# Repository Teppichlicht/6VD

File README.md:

# 6VD
6VDproduct_development

First Changes in Github:
Codesharing for multiuserprogramming in 6VD

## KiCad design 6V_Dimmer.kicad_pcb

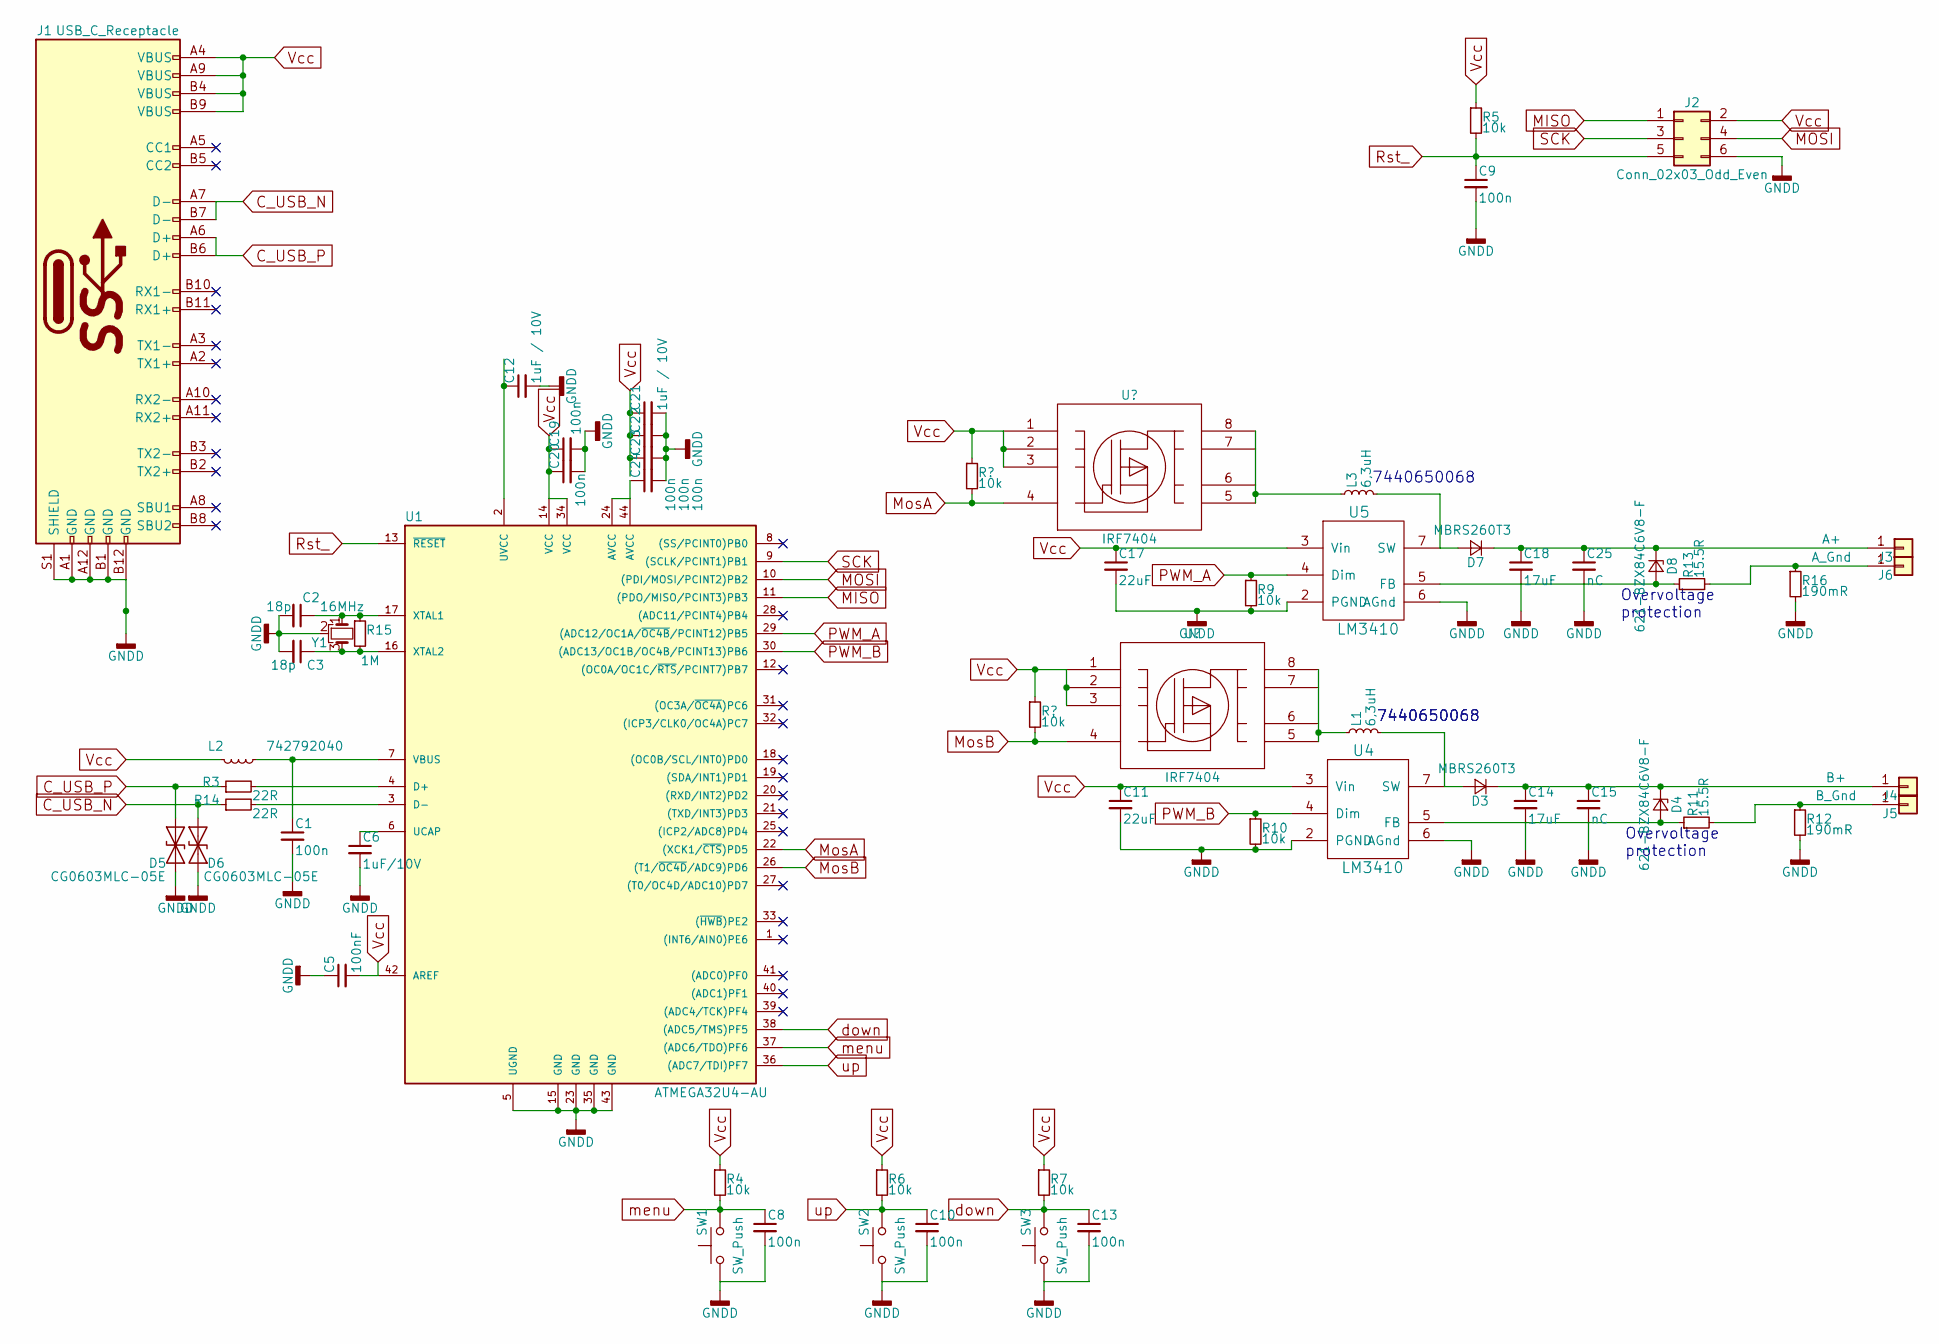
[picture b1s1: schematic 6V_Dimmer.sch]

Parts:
C1, C8, C9, C10, C13, C19, C20, C22, C23, C24: 100n; C_0805_HandSoldering
C2, C3: 18p; C_0805_HandSoldering
C5: 100nF; C_0805_HandSoldering
C6: 1uF/10V; C_0805_HandSoldering
C11, C17: 22uF; C_0805_HandSoldering
C12, C21: 1uF / 10V; C_0805_HandSoldering
C14, C18: 17uF; C_0805_HandSoldering
C15, C25: nC; C_0805_HandSoldering
D3, D7: MBRS260T3; D_SMB
D4, D8: 621-BZX84C6V8-F; D_SOT-23_ANK
D5, D6: CG0603MLC-05E; D_0603
J1: USB_C_Receptacle; USB_C_Receptacle_Amphenol_12401548E4-2A_CircularHoles
J2: Conn_02x03_Odd_Even; Pin_Header_Straight_2x03_Pitch2.54mm
J3: A+; SolderWirePad_single_1-5mmDrill
J4: B+; SolderWirePad_single_1-5mmDrill
J5: B_Gnd; SolderWirePad_single_1-5mmDrill
J6: A_Gnd; SolderWirePad_single_1-5mmDrill
L1, L3: 6,3uH; L_10.4x10.4_H4.8
L2: 742792040; L_0805_HandSoldering
R3, R14: 22R; R_0805_HandSoldering
R4, R5, R6, R7, R9, R10: 10k; R_0805_HandSoldering
R11, R13: 15.5R; R_0805_HandSoldering
R12, R16: 190mR; R_0805_HandSoldering
R15: 1M; R_0805_HandSoldering
SW1, SW2, SW3: SW_Push; SW_SPST_Panasonic_EVQPL_3PL_5PL_PT_A08
U1: ATMEGA32U4-AU; TQFP-44_10x10mm_Pitch0.8mm
U4, U5: LM3410; MSOP-8-1EP_3x3mm_Pitch0.65mm
Y1: 16MHz; Crystal_SMD_Abracon_ABM3B-4pin_5.0x3.2mm

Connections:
C_USB_N: D6.1 (A1), J1.A7 (D-), J1.B7 (D-), R14.1
C_USB_P: D5.1 (A1), J1.A6 (D+), J1.B6 (D+), R3.1
GNDD: C1.2, C2.2, C3.2, C5.1, C6.2, C8.2, C9.2, C10.2, C11.2, C12.2, C13.2, C14.2, C15.2, C17.2, C18.2, C19.2, C20.2, C21.2, C22.2, C23.2, C24.2, C25.2, D5.2 (A2), D6.2 (A2), J1.A1 (GND), J1.A12 (GND), J1.B1 (GND), J1.B12 (GND), J1.S1 (SHIELD), J2.6, R9.2, R10.2, R12.2, R16.2, SW1.1, SW2.1, SW3.1, U1.5 (UGND), U1.15 (GND), U1.23 (GND), U1.35 (GND), U1.43 (GND), U4.2 (PGND), U4.6 (AGnd), U5.2 (PGND), U5.6 (AGnd), Y1.2
MISO: J2.1, U1.11 ((PDO/MISO/PCINT3)PB3)
MOSI: J2.4, U1.10 ((PDI/MOSI/PCINT2)PB2)
unnamed: C1.1, L2.1, U1.7 (VBUS)
unnamed: C2.1, R15.1, U1.17 (XTAL1), Y1.1
unnamed: C3.1, R15.2, U1.16 (XTAL2), Y1.3
unnamed: C6.1, U1.6 (UCAP)
unnamed: C12.1, U1.2 (UVCC)
unnamed: C14.1, C15.1, D3.1 (K), D4.1 (K), J4.1
unnamed: C18.1, C25.1, D7.1 (K), D8.1 (K), J3.1
unnamed: C24.1, U1.24 (AVCC), U1.44 (AVCC)
unnamed: D3.2 (A), L1.2, U4.7 (SW)
unnamed: D4.2 (A), R11.1, U4.5 (FB)
unnamed: D7.2 (A), L3.2, U5.7 (SW)
unnamed: D8.2 (A), R13.1, U5.5 (FB)
unnamed: J5.1, R11.2, R12.1
unnamed: J6.1, R13.2, R16.1
unnamed: R3.2, U1.4 (D+)
unnamed: R14.2, U1.3 (D-)
PWM_A: R9.1, U1.29 ((ADC12/OC1A/~OC4B~/PCINT12)PB5), U5.4 (Dim)
PWM_B: R10.1, U1.30 ((ADC13/OC1B/OC4B/PCINT13)PB6), U4.4 (Dim)
Rst_: C9.1, J2.5, R5.2, U1.13 (~RESET~)
SCK: J2.3, U1.9 ((SCLK/PCINT1)PB1)
Vcc: C5.2, C11.1, C17.1, C19.1, C20.1, C21.1, C22.1, C23.1, J1.A4 (VBUS), J1.A9 (VBUS), J1.B4 (VBUS), J1.B9 (VBUS), J2.2, L1.1, L2.2, L3.1, R4.1, R5.1, R6.1, R7.1, U1.14 (VCC), U1.34 (VCC), U1.42 (AREF), U4.3 (Vin), U5.3 (Vin)
down: C13.1, R7.2, SW3.2, U1.38 ((ADC5/TMS)PF5)
menu: C8.1, R4.2, SW1.2, U1.37 ((ADC6/TDO)PF6)
up: C10.1, R6.2, SW2.2, U1.36 ((ADC7/TDI)PF7)

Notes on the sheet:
7440650068
Overvoltage protection

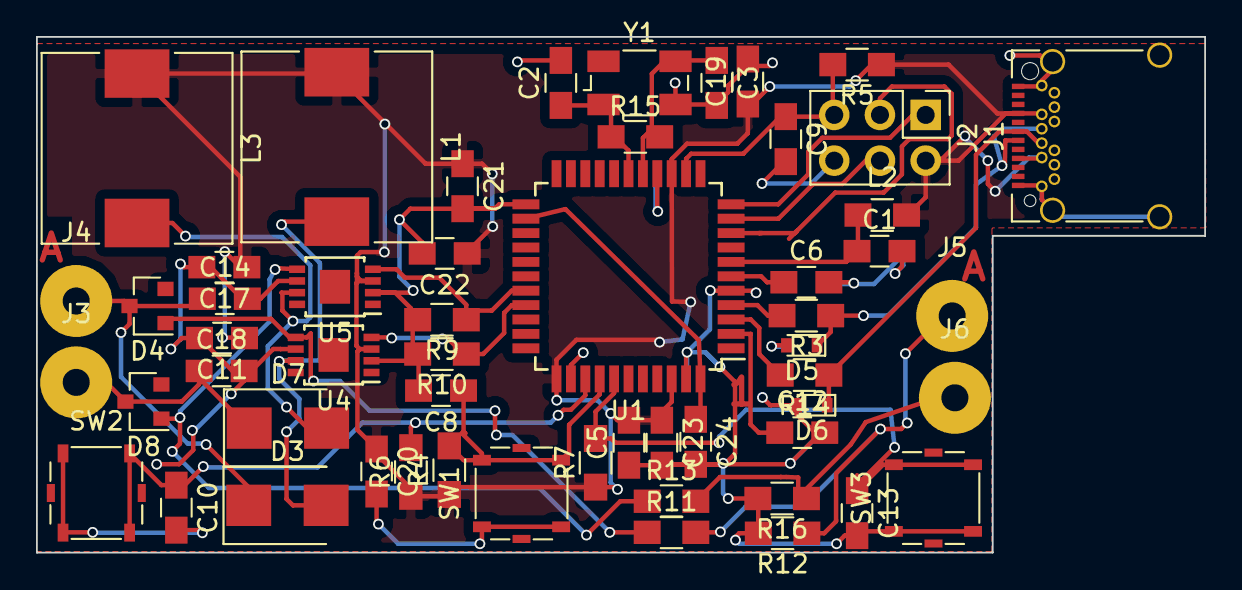
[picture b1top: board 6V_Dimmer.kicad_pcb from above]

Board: 2 copper layers, 64.9 x 28.6 mm, 55 parts (0 on the bottom side), 29 nets.

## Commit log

2018-05-29 Update README.md
    blubb
2018-05-30 Update button.c
    Button.c auf active-low buttons umgestellt und big fat error entfernt
2018-05-31 Add files via upload
    1. version completecode, debugerrors included....not tested yet.
